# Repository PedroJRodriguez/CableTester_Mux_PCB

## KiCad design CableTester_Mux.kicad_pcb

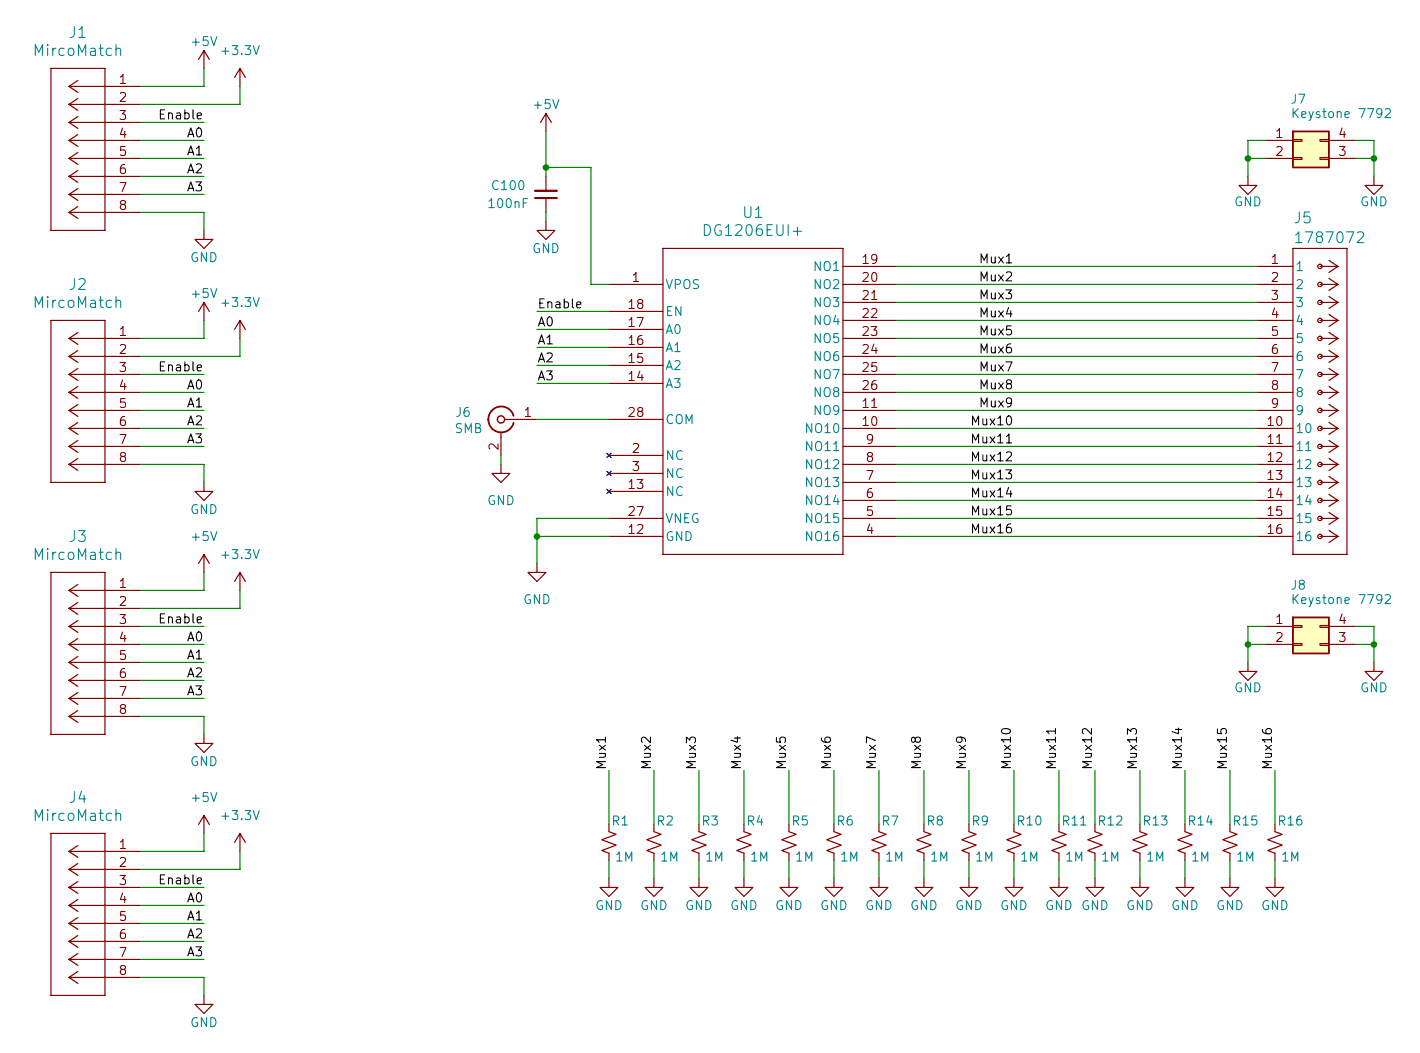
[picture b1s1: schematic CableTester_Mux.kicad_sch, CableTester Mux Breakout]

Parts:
C100: 100nF; C_0805_2012Metric_Pad1.18x1.45mm_HandSolder
J1, J2, J3, J4: MircoMatch; CONN_7-188275-8_TYC
J5: 1787072; CONN_1787072_PXC
J6: SMB; CONN_142146_AMP
J7, J8: Keystone 7792; KEYSTONE_7792
R1, R2, R3, R4, R5, R6, R7, R8, R9, R10, R11, R12, R13, R14, R15, R16: 1M; R_0603_1608Metric_Pad0.98x0.95mm_HandSolder
U1: DG1206EUI+; TSSOP-28_4.4x9.7mm_P0.65mm

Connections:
+3.3V: J1.2, J2.2, J3.2, J4.2
+5V: C100.2, J1.1, J2.1, J3.1, J4.1, U1.1 (VPOS)
/A0: J1.4, J2.4, J3.4, J4.4, U1.17 (A0)
/A1: J1.5, J2.5, J3.5, J4.5, U1.16 (A1)
/A2: J1.6, J2.6, J3.6, J4.6, U1.15 (A2)
/A3: J1.7, J2.7, J3.7, J4.7, U1.14 (A3)
/Enable: J1.3, J2.3, J3.3, J4.3, U1.18 (EN)
/Mux1: J5.1, R1.1, U1.19 (NO1)
/Mux2: J5.2, R2.1, U1.20 (NO2)
/Mux3: J5.3, R3.1, U1.21 (NO3)
/Mux4: J5.4, R4.1, U1.22 (NO4)
/Mux5: J5.5, R5.1, U1.23 (NO5)
/Mux6: J5.6, R6.1, U1.24 (NO6)
/Mux7: J5.7, R7.1, U1.25 (NO7)
/Mux8: J5.8, R8.1, U1.26 (NO8)
/Mux9: J5.9, R9.1, U1.11 (NO9)
/Mux10: J5.10, R10.1, U1.10 (NO10)
/Mux11: J5.11, R11.1, U1.9 (NO11)
/Mux12: J5.12, R12.1, U1.8 (NO12)
/Mux13: J5.13, R13.1, U1.7 (NO13)
/Mux14: J5.14, R14.1, U1.6 (NO14)
/Mux15: J5.15, R15.1, U1.5 (NO15)
/Mux16: J5.16, R16.1, U1.4 (NO16)
GND: C100.1, J1.8, J2.8, J3.8, J4.8, J6.2 (Ext), J6.3 (Ext), J6.4 (Ext), J6.5 (Ext), J7.1, J7.2, J7.3, J7.4, J8.1, J8.2, J8.3, J8.4, R1.2, R2.2, R3.2, R4.2, R5.2, R6.2, R7.2, R8.2, R9.2, R10.2, R11.2, R12.2, R13.2, R14.2, R15.2, R16.2, U1.12 (GND), U1.27 (VNEG)
unnamed: J6.1 (In), U1.28 (COM)

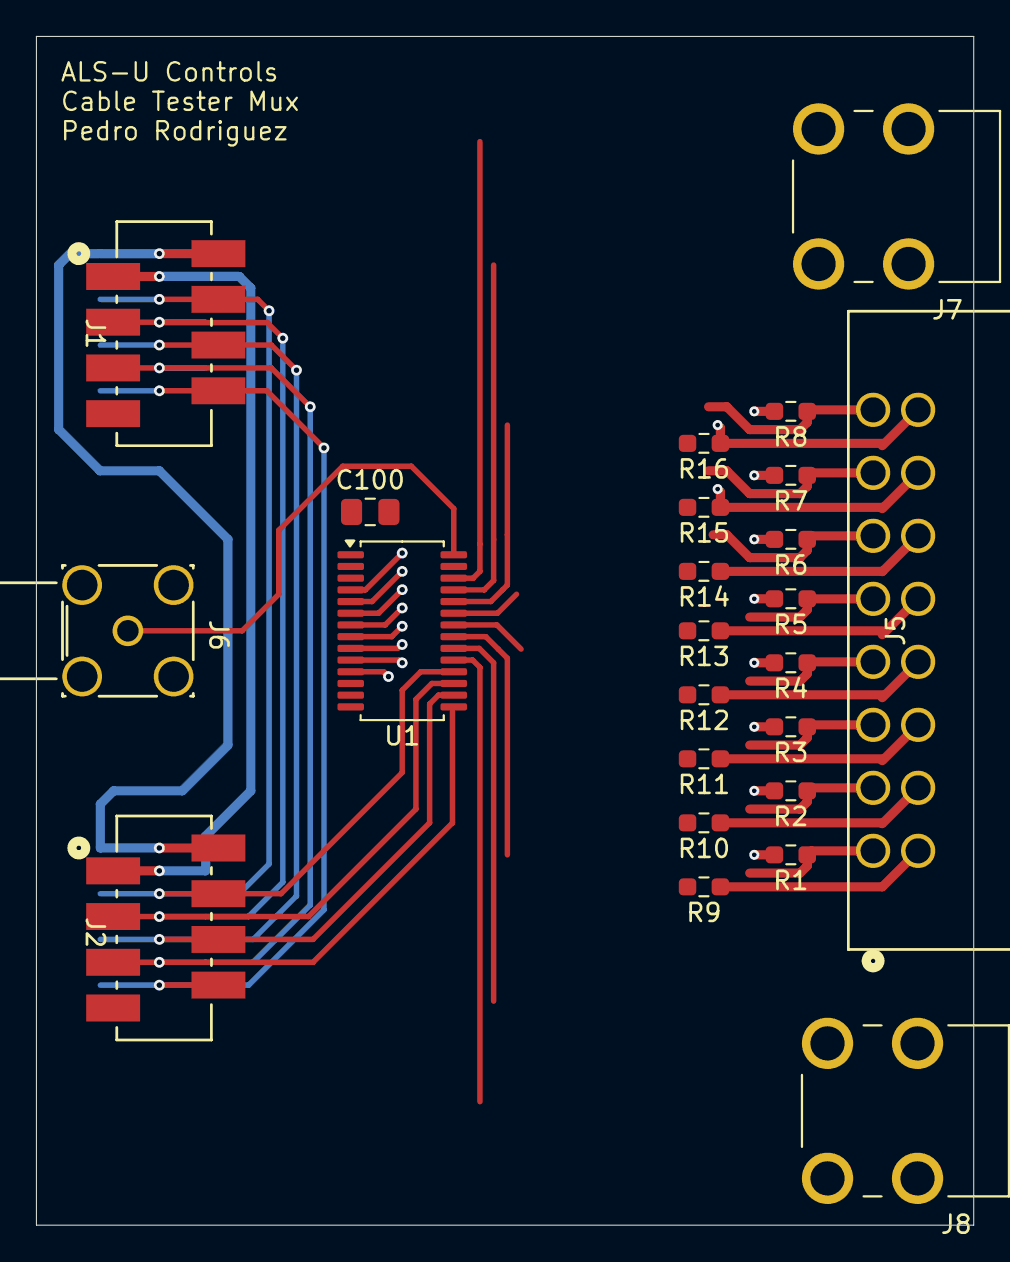
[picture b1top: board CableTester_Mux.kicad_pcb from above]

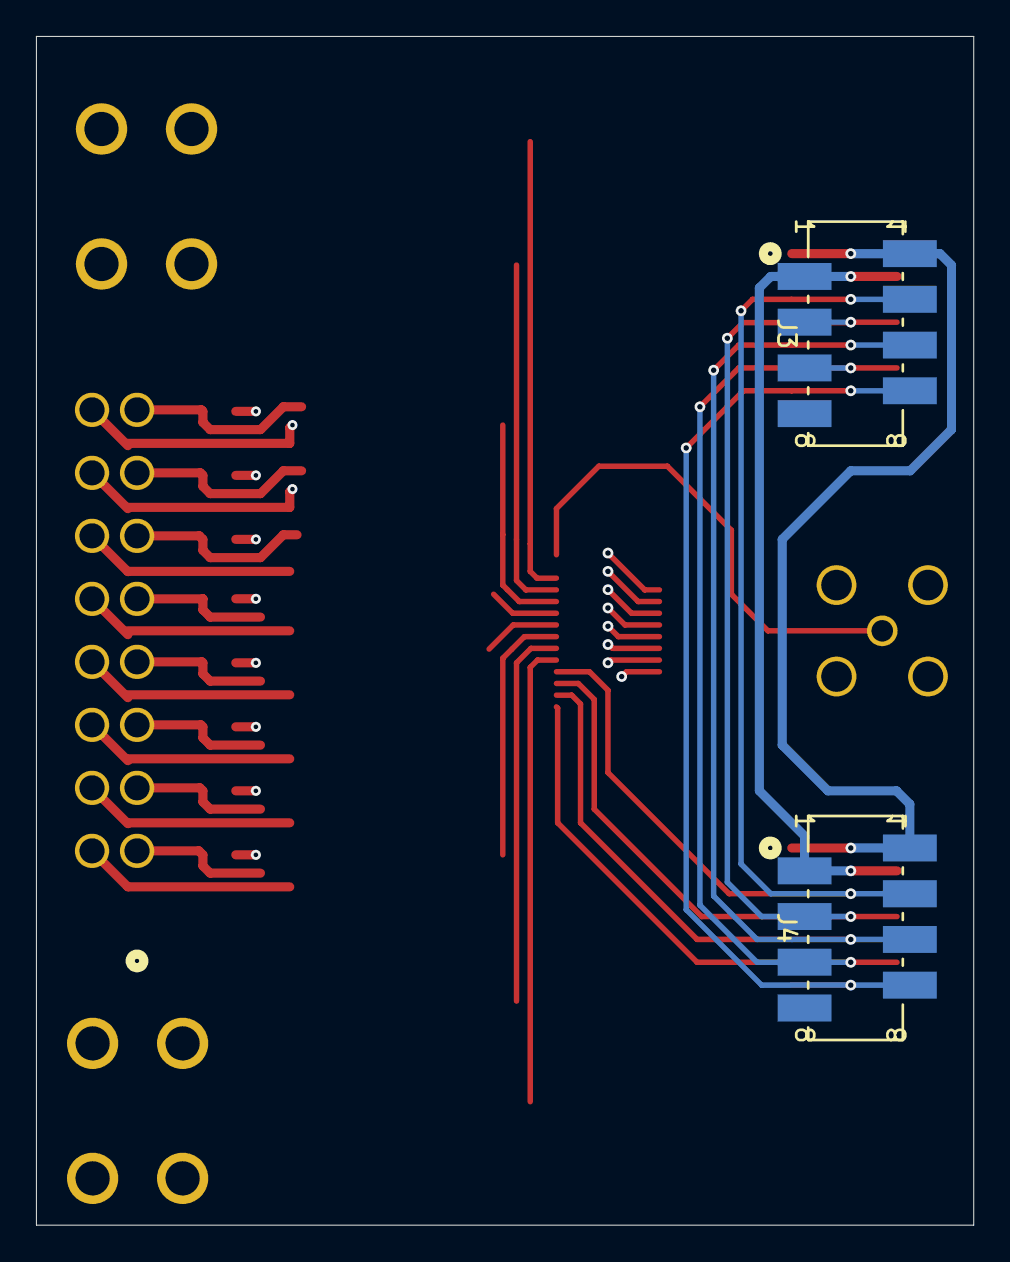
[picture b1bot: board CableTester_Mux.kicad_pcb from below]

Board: 2 copper layers, 52.1 x 66.0 mm, 26 parts (2 on the bottom side), 25 nets.

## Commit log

2025-07-23 inital commit
    needs:
    lib clean up
    routing
2025-08-05 Fixed/Completed Initial Libraries
    -Completed initial libraries
    -Updated schematic and layout with part metadata
2025-08-07 updated lib links and metadata
2025-08-12 adding 3dmodels and symbol lib
2025-08-20 Added filtering components for AC coupled UART to schematic
    Added DC blocking cap and DC re-biasing resistors to schematic.
2025-08-20 Updated Schematics with filter for AC UART signaling
2025-09-03 Updated Layout and added 3dmodel
2025-09-04 Updated Routing
2025-09-04 Removed DC-Blocking filter and update schmatic and layout
